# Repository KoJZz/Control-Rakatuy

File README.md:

# Control-Rakatuy

Repository Control Rakata

## Struktur Folder

* **.git/**: Git configuration (Do not modify)
* **Hardware/**: KiCad PCB layout and schematic files. Nanti buat folder baru aja per project
* **Firmware/**: Firmware yang dipake
* **Docs/**: Documentation
* **Exports/**: (Gerbers, BOM, and PDF schematics)
* **testing/**: ngetes repo

---

### Cloning to a New Machine
To pull this repository into a new local folder:
```bash
git clone https://github.com/KoJZz/Control-Rakatuy

```
### Upload konten baru
```bash
git pull origin main # pull updatean terbaru dari repo
git add . # add file terbaru yang udah dibuat
git commit -m "Update: [Component Name] - Added power stage layout" # commiting
git push origin main # push ke repo

```

### Video tutorial version control
https://www.youtube.com/watch?v=YCKeqBlQyJQ

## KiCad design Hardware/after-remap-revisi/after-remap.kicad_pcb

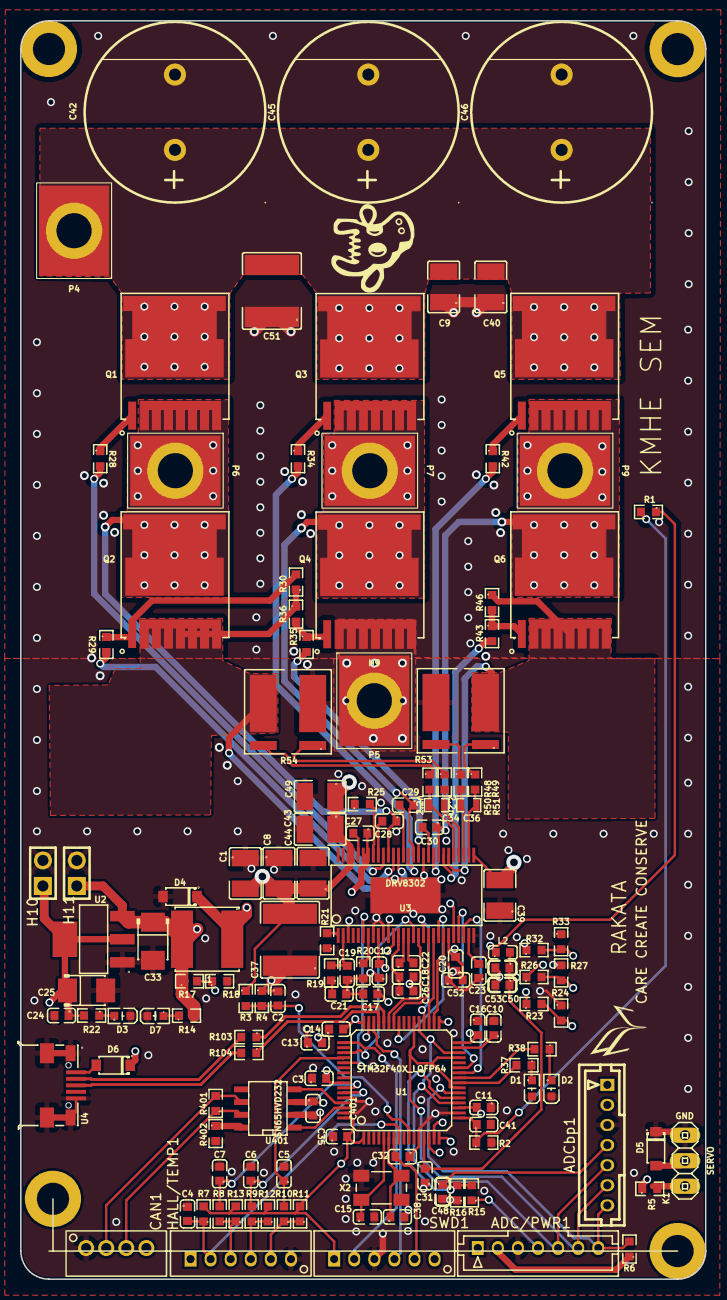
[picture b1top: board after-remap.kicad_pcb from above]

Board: 4 copper layers, 68.2 x 125.3 mm, 146 parts (0 on the bottom side), 99 nets.

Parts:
ADC/PWR1: PWR_COMM; CONN-TH_B7B-PH-K-S-LF-SN
ADCbp1: PWR_COMM; CONN-TH_B7B-PH-K-S-LF-SN
C1, C8, C9, C39, C40, C43, C44, C49: 10u,100V; C1210
C2, C3, C27, C32, C48: 100n; C0603
C4, C5, C6, C7: 4n7; C0603
C10, C11, C12, C13, C14, C16, C17, C18, C20, C23, C24, C26, C31, C35, C41, C50, C52, C401: 2.2u; C0603
C15, C38: 15p; C0603
C19: 120p; C0603
C21: 6.8n; C0603
C22: 22n; C0603
C25, C33: 100u; CAP-SMD_L3.5-W2.8-R-RD
C28, C29, C30, C53: 220n; C0603
C34, C36: 2.2n; SMD-0603_c
C37, C51: 15u,100V; C2220
C42, C45, C46: 680u; CAP-TH_BD18.0-P7.50-D1.2-FD
CAN1: CANBUS; CONN-TH_B4B-PH-K-S
D1: GREEN; LED0603-R-RD_WHITE
D2: RED; LED0603-R-RD_WHITE
D3, D7: LED; LED0603-R-RD_WHITE
D4, D6: SOD-123_L2.8-W1.8-LS3.7-RD
D5: TVS 5V; SOD-123_L2.8-W1.8-LS3.7-RD
H1, H2, H3, H4, H6, H7, H8: MountingHole; MountingHole_3.2mm_M3_DIN965_Pad
H5, H9: MountingHole_Pad; MountingHole_3.2mm_M3_DIN965_Pad
H10, H11: Header-Male-2.54_1x2; HDR-TH_2P-P2.54-V-M-1
HALL/TEMP1: HALL/Encoder; CONN-TH_B6B-PH-K-S
K1: SERVO; pinhead-1X03
L1: 22u; IND-SMD_L6.0-W6.0
L2: BLM18AG601SN1D; L0603
P4: IN+; PAD
P5: IN-; PAD
P6: MOTOR1; PAD
P7: MOTOR2; PAD
P9: MOTOR3; PAD
Q1, Q2, Q3, Q4, Q5, Q6: IPT007N06NATMA1; HSOF-8_IPT007N06N
R1: NTC 10k; R0603
R2, R6, R7, R8, R9, R10, R20, R402: 10k; R0603
R3, R15, R16, R23, R26, R30, R32, R36, R46: 39k; R0603
R4, R5, R11, R12, R13, R14, R22, R24, R27, R33: 2k2; R0603
R17: 18k; R0603
R18: 3k3; R0603
R19: 15k; R0603
R21: 220k; R0603
R25: 1M; R0603
R28, R29, R34, R35, R42, R43: 4R7; R0603
R37, R38, R48, R49, R50, R51: 100R; R0603
R53, R54: WSLP27262L000FEA; R2726
R103, R104: 22R; R0603
R401: NI; R0603
SWD1: SWD; CONN-TH_B6B-PH-K-S
U1: STM32F40X_LQFP64; lqfp64_pad_mod
U2: TC2117; SOT-223_L6.5-W3.5-P2.30-LS7.0-BR
U3: DRV8302; TSSOP-56-PP
U4: MICROQTJ; MICRO-USB-SMD_MICROQTJ-5P
U401: SN65HVD232; SOIC-8-W
X2: 5TJ480000NYLBC; CRYSTAL-SMD_4P-L5.0-W3.2-BL

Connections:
+5V: ADC/PWR1.1, ADCbp1.1, C33.1, CAN1.4, D5.2 (K), D6.1 (K), H11.1, HALL/TEMP1.1, K1.2 (PM), L1.2, R14.2, R17.1, U2.3 (VIN)
/ADC1: ADC/PWR1.4, R15.1
/ADC1_f: ADCbp1.4, C48.1, R15.2, R16.2, U1.21 (PA5(ADC12_IN5/DAC2_OUT))
/CAN bus transceiver/CANH: CAN1.3, R401.1, U401.7 (CANH)
/CAN bus transceiver/CANL: CAN1.2, R401.2, U401.6 (CANL)
/CAN bus transceiver/CAN_RX: U1.61 (PB8), U401.4 (RXD)
/CAN bus transceiver/CAN_TX: U1.62 (PB9), U401.1 (TXD)
/D+: R104.2, U4.3 (D+)
/D-: R103.2, U4.2 (D-)
/Filters/HALL1_IN: HALL/TEMP1.3, R8.1, R13.1
/Filters/HALL1_OUT: C7.1, R8.2, U1.58 (PB6)
/Filters/HALL2_IN: HALL/TEMP1.4, R9.1, R12.1
/Filters/HALL2_OUT: C6.1, R9.2, U1.59 (PB7)
/Filters/HALL3_IN: HALL/TEMP1.5, R10.1, R11.1
/Filters/HALL3_OUT: C5.1, R10.2, U1.52 (PC11)
/Filters/TEMP_MOTOR: C4.2, HALL/TEMP1.2, R7.1, U1.8 (PC0(ADC123_IN10))
/MCU/ADC_TEMP: C41.1, R1.2, R2.1, U1.17 (PA3(ADC123_IN3))
/MCU/AN_IN: C2.2, R3.2, R4.2, U1.10 (PC2(ADC123_IN12))
/MCU/BR_SO1: U1.27 (PB1(ADC12_IN9)), U3.25 (SO1)
/MCU/BR_SO2: U1.26 (PB0(ADC12_IN8)), U3.26 (SO2)
/MCU/DC_CAL: U1.33 (PB12), U3.12 (DC_CAL)
/MCU/EN_GATE: U1.51 (PC10), U3.16 (EN_GATE)
/MCU/FAULT: U1.53 (PC12), U3.6 (FAULT)
/MCU/H1: U1.43 (PA10), U3.17 (INH_A)
/MCU/H2: U1.42 (PA9(OTG_FS_VBUS)), U3.19 (INH_B)
/MCU/H3: U1.41 (PA8), U3.21 (INH_C)
/MCU/L1: U1.36 (PB15), U3.18 (INL_A)
/MCU/L2: U1.35 (PB14), U3.20 (INL_B)
/MCU/L3: U1.34 (PB13(OTG_HS_VBUS)), U3.22 (INL_C)
/MCU/LED_GREEN: R37.2, U1.24 (PC4(ADC12_IN14))
/MCU/LED_RED: R38.2, U1.25 (PC5(ADC12_IN15))
/MCU/SENS1: R23.2, R24.2, U1.16 (PA2(ADC123_IN2))
/MCU/SENS2: R26.2, R27.2, U1.15 (PA1(ADC123_IN1))
/MCU/SENS3: R32.2, R33.2, U1.14 (PA0(ADC123_IN0/WKUP))
/MCU/SERVO: C3.2, R5.1, U1.57 (PB5)
/MCU/X2-1: C15.1, U1.5 (PH0-OSC_IN), X2.1
/MCU/X2-2: C38.1, U1.6 (PH1-OSC_OUT), X2.3
/MISO_RX_SCL: ADC/PWR1.7, ADCbp1.7, R6.2, U1.22 (PA6(ADC12_IN6))
/Mosfet driver/M_H1: R28.2, U3.47 (GH_A)
/Mosfet driver/M_H2: R34.2, U3.42 (GH_B)
/Mosfet driver/M_H3: R42.2, U3.37 (GH_C)
/Mosfet driver/M_L1: R29.2, U3.45 (GL_A)
/Mosfet driver/M_L2: R35.2, U3.40 (GL_B)
/Mosfet driver/M_L3: R43.2, U3.35 (GL_C)
/Mosfet driver/SH1_A: R48.1, R54.2
/Mosfet driver/SH1_B: R49.1, R54.1
/Mosfet driver/SH2_A: R50.1, R53.2
/Mosfet driver/SH2_B: R51.1, R53.1
/Power MOSFETS/Q1-g: Q1.1 (G), R28.1
/Power MOSFETS/Q1-s_Q2-d: C28.1, H6.1, P6.1, Q1.2 (S), Q2.3 (D), R32.1, U3.46 (SH_A)
/Power MOSFETS/Q2-g: Q2.1 (G), R29.1, R30.2
/Power MOSFETS/Q2-s: Q2.2 (S), R30.1, R36.1, R54.4, U3.44 (SL_A)
/Power MOSFETS/Q3-g: Q3.1 (G), R34.1
/Power MOSFETS/Q3-s_Q4-d: C29.1, H7.1, P7.1, Q3.2 (S), Q4.3 (D), R26.1, U3.41 (SH_B)
/Power MOSFETS/Q4-g: Q4.1 (G), R35.1, R36.2
/Power MOSFETS/Q5-g: Q5.1 (G), R42.1
/Power MOSFETS/Q5-s_Q6-d: C30.1, H8.1, P9.1, Q5.2 (S), Q6.3 (D), R23.1, U3.36 (SH_C)
/Power MOSFETS/Q6-g: Q6.1 (G), R43.1, R46.2
/Power MOSFETS/Q6-s: Q6.2 (S), R46.1, R53.3, U3.34 (SL_C)
/RX_SCL_MOSI: ADC/PWR1.6, ADCbp1.6, U1.23 (PA7(ADC12_IN7)), U1.29 (PB10), U1.38 (PC7)
/TX_SDA: ADC/PWR1.5, ADCbp1.5, U1.20 (PA4(ADC12_IN4/DAC1_OUT)), U1.30 (PB11), U1.37 (PC6)
/USB+: R104.1, U1.45 (PA12)
/USB-: R103.1, U1.44 (PA11)
GND: ADC/PWR1.3, ADCbp1.3, C1.1, C2.1, C3.1, C4.1, C5.2, C6.2, C7.2, C8.1, C9.1, C10.1, C11.1, C12.1, C13.1, C14.1, C15.2, C16.2, C17.2, C18.2, C19.1, C20.1, C21.1, C23.1, C24.2, C25.2, C26.2, C31.1, C32.1, C33.2, C35.1, C37.1, C38.2, C39.1, C40.1, C41.2, C42.2, C43.2, C44.2, C45.2, C46.2, C48.2, C49.2, C50.2, C51.1, C52.1, C53.2, C401.2, CAN1.1, D1.2 (K), D2.2 (K), D3.2 (K), D4.2 (A), D5.1 (A), D7.2 (K), H9.1, H10.2, H11.2, HALL/TEMP1.6, K1.3, P5.1, Q4.2 (S), R2.2, R4.1, R16.1, R18.2, R20.2, R21.1, R24.1, R25.1, R27.1, R33.1, R53.4, R54.3, R402.2, SWD1.3, U1.12 (VSSA), U1.18 (VSS), U1.60 (BOOT0(VPP)), U1.63 (VSS), U2.1 (GND), U3.8 (M_PWM), U3.10 (GAIN), U3.28 (AGND), U3.39 (SL_B), U3.57 (GND(POWER_PAD)), U4.5 (GND), U4.6 (SH1), U4.7 (SH2), U4.8 (SH3), U4.9 (SH4), U401.2 (VSS), X2.2 (GND), X2.4 (GND)
NRST: C32.2, SWD1.5, U1.7 (NRST)
unnamed: C21.2, R19.1
unnamed: D1.1 (A), R37.1
unnamed: D2.1 (A), R38.1
unnamed: D3.1 (A), R22.1
unnamed: C27.1, D4.1 (K), L1.1, U3.50 (PH), U3.51 (PH)
unnamed: D6.2 (A), U4.1 (VBUS)
unnamed: D7.1 (A), R14.1
unnamed: K1.1, R5.2
unnamed: C16.1, U1.31 (VCAP1)
unnamed: C17.1, U1.47 (VCAP2)
unnamed: C23.2, U3.27 (AVDD)
unnamed: R25.2, U3.49 (BIAS)
unnamed: C28.2, U3.48 (BST_A)
unnamed: C29.2, U3.43 (BST_B)
unnamed: C27.2, U3.52 (BST_BK)
unnamed: C30.2, U3.38 (BST_C)
unnamed: C19.2, R19.2, U3.2 (COMP)
unnamed: C22.1, U3.14 (CP1)
unnamed: C22.2, U3.15 (CP2)
unnamed: R20.1, U3.7 (DTC)
unnamed: C20.2, C52.2, U3.11 (OC_ADJ), U3.23 (DVDD)
unnamed: C18.1, C26.1, U3.13 (GVDD)
unnamed: R21.2, U3.1 (RT_CLK)
unnamed: C34.1, R48.2, U3.33 (SN1)
unnamed: C36.1, R50.2, U3.31 (SN2)
unnamed: C34.2, R49.2, U3.32 (SP1)
unnamed: C36.2, R51.2, U3.30 (SP2)
unnamed: R17.2, R18.1, U3.3 (VSENSE)
unnamed: R402.1, U401.8 (Rs)
SWCLK: SWD1.2, U1.49 (PA14(JTCK-SWCLK))
SWDIO: SWD1.4, U1.46 (PA13(JTMS-SWDIO))
VCC: ADC/PWR1.2, ADCbp1.2, C10.2, C11.2, C12.2, C13.2, C14.2, C24.1, C25.1, C35.2, C401.1, H10.1, L2.1, R1.1, R6.1, R7.2, R11.2, R12.2, R13.2, R22.2, SWD1.1, U1.1 (VBAT), U1.19 (VDD), U1.32 (VDD), U1.48 (VDD), U1.64 (VDD), U2.2 (VOUT), U2.4 (VOUT), U3.9 (M_OC), U401.3 (VDD)
VDDA: C31.2, C50.1, C53.1, L2.2, U1.13 (VDDA), U3.24 (REF)
V_SUPPLY: C1.2, C8.2, C9.2, C37.2, C39.2, C40.2, C42.1, C43.1, C44.1, C45.1, C46.1, C49.1, C51.2, H5.1, P4.1, Q1.3 (D), Q3.3 (D), Q5.3 (D), R3.1, U3.29 (PVDD1), U3.53 (PVDD2), U3.54 (PVDD2)

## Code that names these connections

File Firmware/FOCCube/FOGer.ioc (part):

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Mcu.Name=STM32F405RGTx
Mcu.Package=LQFP64
Mcu.UserName=STM32F405RGTx
PA10.Signal=S_TIM1_CH3
PA11.Mode=Device_Only
PA11.Signal=USB_OTG_FS_DM
PA12.Mode=Device_Only
PA12.Signal=USB_OTG_FS_DP
PA13.Mode=Serial_Wire
PA13.Signal=SYS_JTMS-SWDIO
PA14.Mode=Serial_Wire
PA14.Signal=SYS_JTCK-SWCLK
PA5.Signal=ADCx_IN5
PA6.GPIOParameters=GPIO_Label
PA6.GPIO_Label=DEADMAN
PA6.Signal=GPIO_Input
PA8.Signal=S_TIM1_CH1
PA9.Signal=S_TIM1_CH2
PB0.Signal=ADCx_IN8
PB1.Signal=ADCx_IN9
PB12.GPIOParameters=GPIO_Label
PB12.GPIO_Label=DC_CAL
PB12.Signal=GPIO_Output
PB13.Mode=PWM Generation1 CH1 CH1N
PB13.Signal=TIM1_CH1N
PB14.Mode=PWM Generation2 CH2 CH2N
PB14.Signal=TIM1_CH2N
PB15.Mode=PWM Generation3 CH3 CH3N
PB15.Signal=TIM1_CH3N
PB6.GPIOParameters=GPIO_ModeDefaultEXTI
PB6.GPIO_ModeDefaultEXTI=GPIO_MODE_IT_RISING_FALLING
PB6.Signal=GPXTI6
PB7.GPIOParameters=GPIO_ModeDefaultEXTI
PB7.GPIO_ModeDefaultEXTI=GPIO_MODE_IT_RISING_FALLING
PB7.Signal=GPXTI7
PC10.GPIOParameters=GPIO_Label
PC10.GPIO_Label=EN_GATE
PC10.Signal=GPIO_Output
PC11.GPIOParameters=GPIO_ModeDefaultEXTI
PC11.GPIO_ModeDefaultEXTI=GPIO_MODE_IT_RISING_FALLING
PC11.Signal=GPXTI11
PC12.GPIOParameters=GPIO_PuPd,GPIO_Label,GPIO_ModeDefaultEXTI
PC12.GPIO_Label=DRV_FAULT
PC12.GPIO_ModeDefaultEXTI=GPIO_MODE_IT_FALLING
PC12.GPIO_PuPd=GPIO_PULLUP
PC12.Signal=GPXTI12
PC2.Signal=ADCx_IN12
PC4.GPIOParameters=GPIO_Label
PC4.GPIO_Label=LED_GREEN
PC4.Signal=GPIO_Output
PC5.GPIOParameters=GPIO_Label
PC5.GPIO_Label=LED_RED
PC5.Signal=GPIO_Output
PH0-OSC_IN.Mode=HSE-External-Oscillator
PH0-OSC_IN.Signal=RCC_OSC_IN
PH1-OSC_OUT.Mode=HSE-External-Oscillator
PH1-OSC_OUT.Signal=RCC_OSC_OUT
RCC.HSE_VALUE=8000000
RCC.SYSCLKFreq_VALUE=168000000
RCC.SYSCLKSource=RCC_SYSCLKSOURCE_PLLCLK
board=custom

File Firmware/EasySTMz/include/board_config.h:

#pragma once

// ===== PWM (Gate driver) pins - TIM1 channels =====
#define PWM_AH PA10
#define PWM_AL PB15

#define PWM_BH PA9
#define PWM_BL PB14

#define PWM_CH PA8
#define PWM_CL PB13

// ===== DRV8302 control pins =====
#define PIN_EN_GATE   PC10
#define PIN_DCCAL     PB12
#define PIN_DRV_FAULT PC12

// ===== Hall sensor pins =====
#define PIN_HALL_A PB6
#define PIN_HALL_B PB7
#define PIN_HALL_C PC11

// ===== Current sense pins =====
#define PIN_CURR_A PB1   // SH1 -> SN1/SP1 -> BR_SO1 -> CURR1 -> Phase A (PHASE_1, Q1/Q2)
#define PIN_CURR_C PB0   // SH2 -> SN2/SP2 -> BR_SO2 -> CURR2 -> Phase C (PHASE_3, Q5/Q6)

// ===== Voltage sense =====
#define PIN_VIN_SENSE PC2

// ===== LEDs =====
#define PIN_LED_GREEN PC4
#define PIN_LED_RED   PC5

// ===== Deadman switch (active-LOW, external pull-up on board) =====
#define PIN_DEADMAN PA6

// ===== Throttle (analog, Vcc-referenced) =====
#define PIN_THROTTLE PA5

// ===== Board electrical constants (from hw_410.h) =====
#define CURRENT_SHUNT_RES   0.001f   // 1 mOhm
#define CURRENT_AMP_GAIN    10.0f
#define VIN_R1              39000.0f
#define VIN_R2              2200.0f
#define V_REG               3.3f
#define PWM_FREQ            20000

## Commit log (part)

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2026-04-11 testing
2026-04-12 folder
2026-04-12 fix typo
2026-04-12 folder baru
2026-04-20 added vesc-4 hardware
2026-04-21 sebelum-coba-fix
2026-04-21 geser via h1_vs yang "short" sh2_b
2026-04-22 22/04/2026
2026-04-22 exported local library
2026-04-22 export footprint & ngapus warning unmatched
2026-04-22 fix text thickness
    widht 0.615mm, height 1mm, thickness 0.153mm
2026-04-22 try drc dari github orang
2026-04-22 fix error2 clearance
    harusnya sesuai sama jlc
2026-04-23 firmware ccllogging
    mau mulai improve algoritma PID
2026-04-24 pindahin sketchbook
    pindahin sketchbook ke folder firmware
2026-04-24 revert
    This reverts commit 5363225a17d2aae300a7f308fe655f067ec562b7.
2026-04-28 coba cari tau harga
2026-04-29 besarin size
2026-04-30 wiring mosfet baru
2026-04-30 rewired mosfet baru di schematic
2026-04-30 -
    This reverts commit 677c41b31d7c264f2526b51b284ce0d322415a8e.
2026-04-30 Revert "besarin size"
    This reverts commit 1f1ec443e13dcadbf9f4db8f2ac1cffe4f152bb3.
2026-04-30 checkpoint
    dimensi pcb default + mosfet baru rewired di schematic
2026-04-30 masukin footprint baru
    buat folder baru dan masukin footprint ke situ. Converted schematic into pcb
2026-05-03 changed mosfet footprint jadi M
2026-05-03 taro mosfet phase 1
2026-05-03 mulai phase 2
2026-05-03 phase 2 placed
2026-05-03 phase 3 kepasang
    mau perbaikin track
2026-05-03 checkpoint sblm perbaikin drc2
2026-05-04 checkpoint
2026-05-04 fix thermal relif
2026-05-06 sebelum ganti via
2026-05-06 changed phase 3
2026-05-06 change phase tengah
2026-05-06 pindahin via untuk perbanyak contact
2026-05-06 done changed via numpuk
2026-05-06 added thermal vias on front mosfets
2026-05-07 ganti kompoinen usb
2026-05-07 ganti schematic
2026-05-07 sebelum ganti komponen
2026-05-07 checkpoint sebelum ngetrace usb
2026-05-07 pindahin d6
2026-05-07 usb kelar trace
2026-05-07 hapus r6 0r sama via
2026-05-07 sebelum pasang d4
2026-05-07 habis pasang d4
2026-05-09 cp0905
2026-05-11 changed inductor
2026-05-12 checkpoint dapetin komponen kristal
2026-05-13 changed crystal x2
2026-05-13 checkpoint mau ganti shunt
2026-05-13 checkpoint ganti shunt
2026-05-13 ganti shunt
2026-05-13 changed c tantalum
2026-05-13 changed 15u 100V footprint
    c37 c51
2026-05-13 mau ganti micro usb
2026-05-13 changed USB
2026-05-13 sebelum ganti kapasitor 1206
2026-05-13 changed capacitor 10u 50V
2026-05-13 cp sebelum ganti 4n7
2026-05-14 cp sebelum ganti 2.2u
2026-05-14 changed footprint 4n7 cap
2026-05-15 pindahin file
2026-05-16 all done
2026-05-16 update mosfet
2026-05-16 fix conn
2026-05-18 chekcpoint 18 mei
2026-05-18 fixed alignment and orientation
2026-05-20 cp20mei
2026-05-23 cp23mei
2026-05-29 cp29mei
2026-06-16 16-06-2026
2026-06-16 Update and rename New Text Document.txt to How to Flash
2026-06-16 kode controller SEM
2026-06-16 upload firmware STM
2026-06-16 upload firmware ke github
2026-06-26 cpcp
2026-06-27 upload firmware
2026-06-27 recover VESG4 firmware
2026-06-27 update firmware
